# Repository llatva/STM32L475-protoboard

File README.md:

## STM32L475 protoboard

Development board for STM32L475 (4-layer board). Includes header for W5500 Ethernet module (SPI bus).

JP2 solder jumper needs to be short-circuited to enable USB VBUS detection (not needed if powered only from microUSB connector). Solder jumper needs to be short-circuited to enable USR1 LED. R8 is NOT to be mounted (USB data line pull-up is not used for this MCU type). Fuse pads are for polyswitch fuses. SMD capacitor pads are for A/D LPF (MCU pins have multiple functions).

Boot selection pin (BOOT0) next to the programming connector should be in normal operation shorted to GND (jumper). This means booting from FLASH.

Connector pinouts are documented on the bottom side of the board (programming interface, SPI interface).

See also the daughterboard, in the subdirectory "STM32daughter".

Designed by Lasse OH3HZB 2023

This work is licensed under a [Creative Commons Attribution-NonCommercial 4.0 International License (CC BY-NC 4.0)](https://creativecommons.org/licenses/by-nc/4.0/).

### RevA ERRATA

* Silkscreen: BOTTOM silkscreen, Ethernet connector's pin next to 3V3 is VDC, not "NC". Actual wiring is correct.

### 3D

### Photo

### Schematic

Open with KiCAD (v.7+) or use [this PDF](STM32L475-protoboard.pdf).

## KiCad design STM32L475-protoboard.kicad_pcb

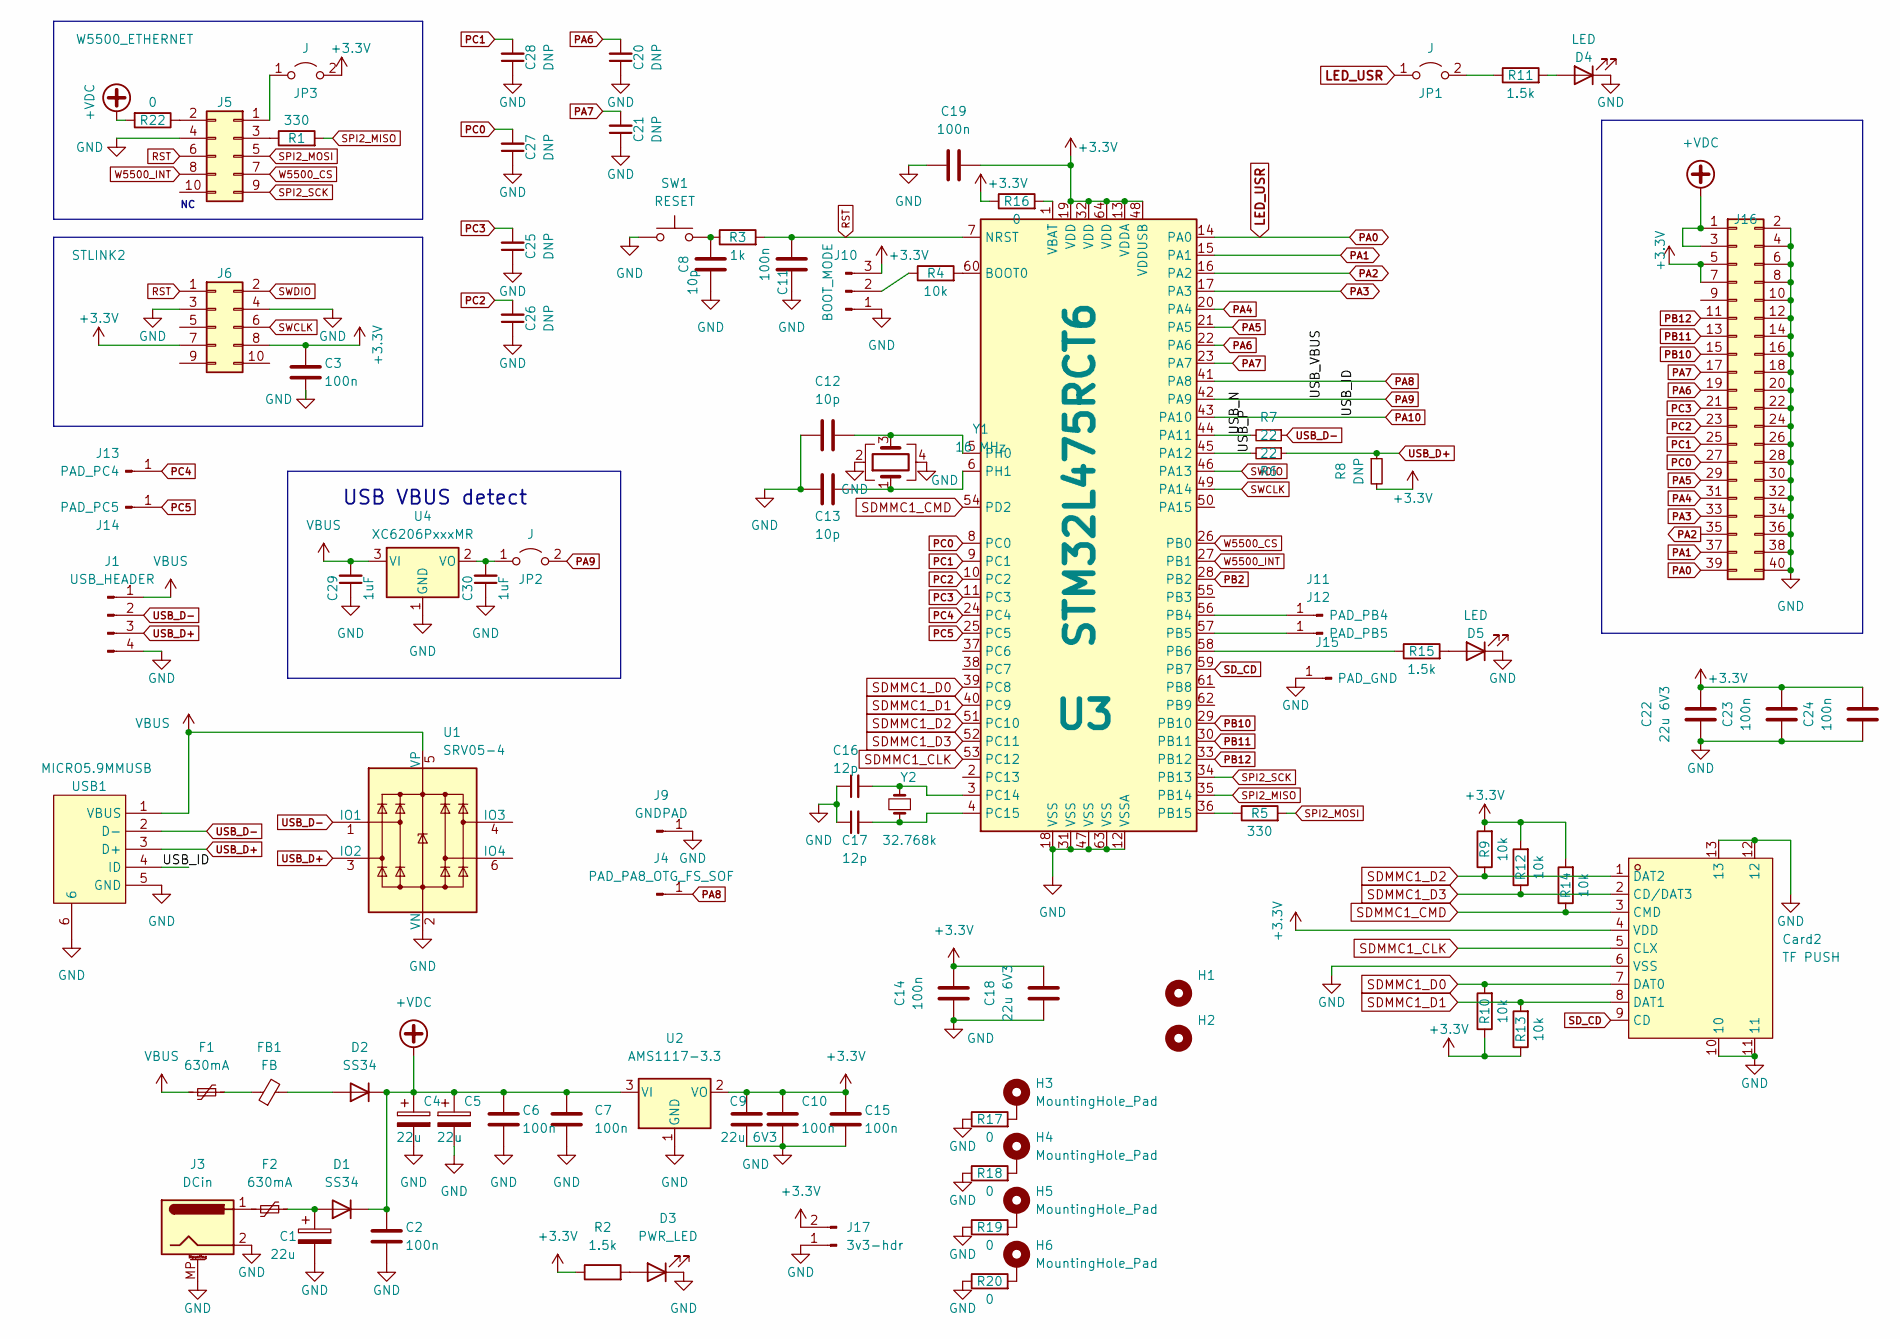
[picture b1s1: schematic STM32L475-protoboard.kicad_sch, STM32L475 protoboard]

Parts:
C1, C4, C5: 22u; C_0805_2012Metric; LCSC C45783
C2, C3, C6, C7, C10, C11, C14, C15, C19, C23, C24: 100n; C_0603_1608Metric; LCSC C14663
C8, C12, C13: 10p; C_0603_1608Metric; LCSC C1634
C9, C18, C22: 22u 6V3; C_0603_1608Metric; LCSC C59461
C16, C17: 12p; C_0603_1608Metric; LCSC C38523
C20, C21, C25, C26, C27, C28: DNP; C_1206_3216Metric_Pad1.33x1.80mm_HandSolder
C29, C30: 1uF; C_0603_1608Metric; LCSC C15849
Card2: TF PUSH; TF-SMD_TF-PUSH; LCSC Part C393941
D1, D2: SS34; D_SMA; LCSC C8678
D3: PWR_LED; LED_0805_2012Metric; LCSC C2297
D4, D5: LED; LED_0603_1608Metric; LCSC C2286
F1, F2: 630mA; R_Axial_DIN0207_L6.3mm_D2.5mm_P7.62mm_Horizontal
FB1: FB; L_0805_2012Metric; LCSC C1015
H1, H2: MountingHole_Pad; MountingHole_2.2mm_M2_DIN965_Pad_TopBottom
H3, H4, H5, H6: MountingHole_Pad; MountingHole_3.2mm_M3_DIN965_Pad_TopBottom
J1: USB_HEADER; PinHeader_1x04_P2.54mm_Vertical
J3: DCin; BarrelJack_Horizontal
J4: PAD_PA8_OTG_FS_SOF; SolderWirePad_1x01_SMD_1x2mm
J5: W5500_ETHERNET; PinSocket_2x05_P2.54mm_Vertical
J6: STLINK2; IDC-Header_2x05_P2.54mm_Vertical
J9: GNDPAD; SolderWirePad_1x01_SMD_1x2mm
J10: BOOT_MODE; PinHeader_1x03_P2.54mm_Vertical
J11: PAD_PB4; SolderWirePad_1x01_SMD_1x2mm
J12: PAD_PB5; SolderWirePad_1x01_SMD_1x2mm
J13: PAD_PC4; SolderWirePad_1x01_SMD_1x2mm
J14: PAD_PC5; SolderWirePad_1x01_SMD_1x2mm
J15: PAD_GND; SolderWirePad_1x01_SMD_1x2mm
J16: Conn_02x20_Odd_Even; PinHeader_2x20_P2.54mm_Vertical
J17: 3v3-hdr; PinHeader_1x02_P2.54mm_Vertical
JP1, JP2, JP3: J; SolderJumper-2_P1.3mm_Open_RoundedPad1.0x1.5mm
R1, R5: 330; R_0603_1608Metric; LCSC C23138
R2, R11, R15: 1.5k; R_0603_1608Metric; LCSC C22843
R3: 1k; R_0603_1608Metric_Pad0.98x0.95mm_HandSolder; LCSC C21190
R4, R9, R10, R12, R13, R14: 10k; R_0603_1608Metric; LCSC C25804
R6, R7: 22; R_0603_1608Metric; LCSC C23345
R8: DNP; R_0603_1608Metric_Pad0.98x0.95mm_HandSolder
R16, R17, R18, R19, R20, R22: 0; R_0603_1608Metric_Pad0.98x0.95mm_HandSolder; LCSC C21189
SW1: RESET; SW_PUSH_6mm_H4.3mm
U1: SRV05-4; SOT-23-6; LCSC C85364
U2: AMS1117-3.3; SOT-223-3_TabPin2; LCSC C6186
U3: STM32L475RCT6; LQFP-64_10x10mm_P0.5mm
U4: XC6206PxxxMR; SOT-23-3; LCSC C5446
USB1: MICRO5.9MMUSB; MICRO-USB-SMD_5P-P0.65-H-F_MICRO5.9MMUSB; LCSC C393940
Y1: 16 MHz; Crystal_SMD_3225-4Pin_3.2x2.5mm; LCSC C13738
Y2: 32.768k; Crystal_SMD_3215-2Pin_3.2x1.5mm; LCSC C32346

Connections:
+3V3: C3.1, C9.1, C10.1, C14.2, C15.1, C18.2, C19.2, C22.2, C23.2, C24.2, Card2.4 (VDD), J6.7, J6.8, J10.3, J16.5, J16.7, J17.2, JP3.2 (B), R2.1, R8.2, R9.2, R10.1, R12.2, R13.1, R14.2, R16.1, U2.2 (VO), U3.13 (VDDA), U3.19 (VDD), U3.32 (VDD), U3.48 (VDDUSB), U3.64 (VDD)
+VDC: C2.1, C4.1, C5.1, C6.1, C7.1, D1.1 (K), D2.1 (K), J16.1, J16.3, R22.2, U2.3 (VI)
/USB_N: R6.2, U3.44 (PA11)
/USB_P: R7.2, U3.45 (PA12)
GND: C1.2, C2.2, C3.2, C4.2, C5.2, C6.2, C7.2, C8.2, C9.2, C10.2, C11.1, C12.1, C13.2, C14.1, C15.2, C16.1, C17.1, C18.1, C19.1, C20.1, C21.1, C22.1, C23.1, C24.1, C25.1, C26.1, C27.1, C28.1, C29.1, C30.1, Card2.6 (VSS), Card2.10, Card2.11, Card2.12, Card2.13, D3.1 (K), D4.1 (K), D5.1 (K), J1.4, J3.2, J3.MP (MountPin), J5.4, J6.3, J6.4, J9.1, J10.1, J15.1, J16.2, J16.4, J16.6, J16.8, J16.10, J16.12, J16.14, J16.16, J16.18, J16.20, J16.22, J16.24, J16.26, J16.28, J16.30, J16.32, J16.34, J16.36, J16.38, J16.40, J17.1, R17.1, R18.1, R19.1, R20.1, SW1.1, U1.2 (VN), U2.1 (GND), U3.12 (VSSA), U3.18 (VSS), U3.31 (VSS), U3.47 (VSS), U3.63 (VSS), U4.1 (GND), USB1.5 (GND), USB1.6, Y1.2, Y1.4
LED_USR: J16.39, JP1.1 (A), U3.14 (PA0)
unnamed: C8.1, R3.1, SW1.2
unnamed: C1.1, D1.2 (A), F2.1
unnamed: D2.2 (A), FB1.2
unnamed: D3.2 (A), R2.2
unnamed: D4.2 (A), R11.2
unnamed: D5.2 (A), R15.2
unnamed: F1.1, FB1.1
unnamed: F2.2, J3.1
unnamed: H3.1, R17.2
unnamed: H4.1, R18.2
unnamed: H5.1, R19.2
unnamed: H6.1, R20.2
unnamed: J5.1, JP3.1 (A)
unnamed: J5.2, R22.1
unnamed: J5.3, R1.1
unnamed: J10.2, R4.1
unnamed: J11.1, U3.56 (PB4)
unnamed: J12.1, U3.57 (PB5)
unnamed: JP1.2 (B), R11.1
unnamed: C30.2, JP2.1 (A), U4.2 (VO)
unnamed: R4.2, U3.60 (BOOT0)
unnamed: R15.1, U3.58 (PB6)
unnamed: R5.1, U3.36 (PB15)
unnamed: C16.2, U3.3 (PC14), Y2.2
unnamed: C17.2, U3.4 (PC15), Y2.1
unnamed: C12.2, U3.5 (PH0), Y1.3
unnamed: C13.1, U3.6 (PH1), Y1.1
unnamed: R16.2, U3.1 (VBAT)
PA1: J16.37, U3.15 (PA1)
PA2: J16.35, U3.16 (PA2)
PA3: J16.33, U3.17 (PA3)
PA4: J16.31, U3.20 (PA4)
PA5: J16.29, U3.21 (PA5)
PA6: C20.2, J16.19, U3.22 (PA6)
PA7: C21.2, J16.17, U3.23 (PA7)
PA8: J4.1, U3.41 (PA8)
PA9: JP2.2 (B), U3.42 (PA9)
PA10: U3.43 (PA10), USB1.4 (ID)
PB2: U3.28 (PB2)
PB10: J16.15, U3.29 (PB10)
PB11: J16.13, U3.30 (PB11)
PB12: J16.11, U3.33 (PB12)
PC0: C27.2, J16.27, U3.8 (PC0)
PC1: C28.2, J16.25, U3.9 (PC1)
PC2: C26.2, J16.23, U3.10 (PC2)
PC3: C25.2, J16.21, U3.11 (PC3)
PC4: J13.1, U3.24 (PC4)
PC5: J14.1, U3.25 (PC5)
RST: C11.2, J5.6, J6.1, R3.2, U3.7 (NRST)
SDMMC1_CLK: Card2.5 (CLX), U3.53 (PC12)
SDMMC1_CMD: Card2.3 (CMD), R14.1, U3.54 (PD2)
SDMMC1_D0: Card2.7 (DAT0), R10.2, U3.39 (PC8)
SDMMC1_D1: Card2.8 (DAT1), R13.2, U3.40 (PC9)
SDMMC1_D2: Card2.1 (DAT2), R9.1, U3.51 (PC10)
SDMMC1_D3: Card2.2 (CD/DAT3), R12.1, U3.52 (PC11)
SD_CD: Card2.9 (CD), U3.59 (PB7)
SPI2_MISO: R1.2, U3.35 (PB14)
SPI2_MOSI: J5.5, R5.2
SPI2_SCK: J5.9, U3.34 (PB13)
SWCLK: J6.6, U3.49 (PA14)
SWDIO: J6.2, U3.46 (PA13)
USB_D+: J1.3, R7.1, R8.1, U1.3 (IO2), USB1.3 (D+)
USB_D-: J1.2, R6.1, U1.1 (IO1), USB1.2 (D-)
VBUS: C29.2, F1.2, J1.1, U1.5 (VP), U4.3 (VI), USB1.1 (VBUS)
W5500_CS: J5.7, U3.26 (PB0)
W5500_INT: J5.8, U3.27 (PB1)

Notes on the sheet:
USB VBUS detect

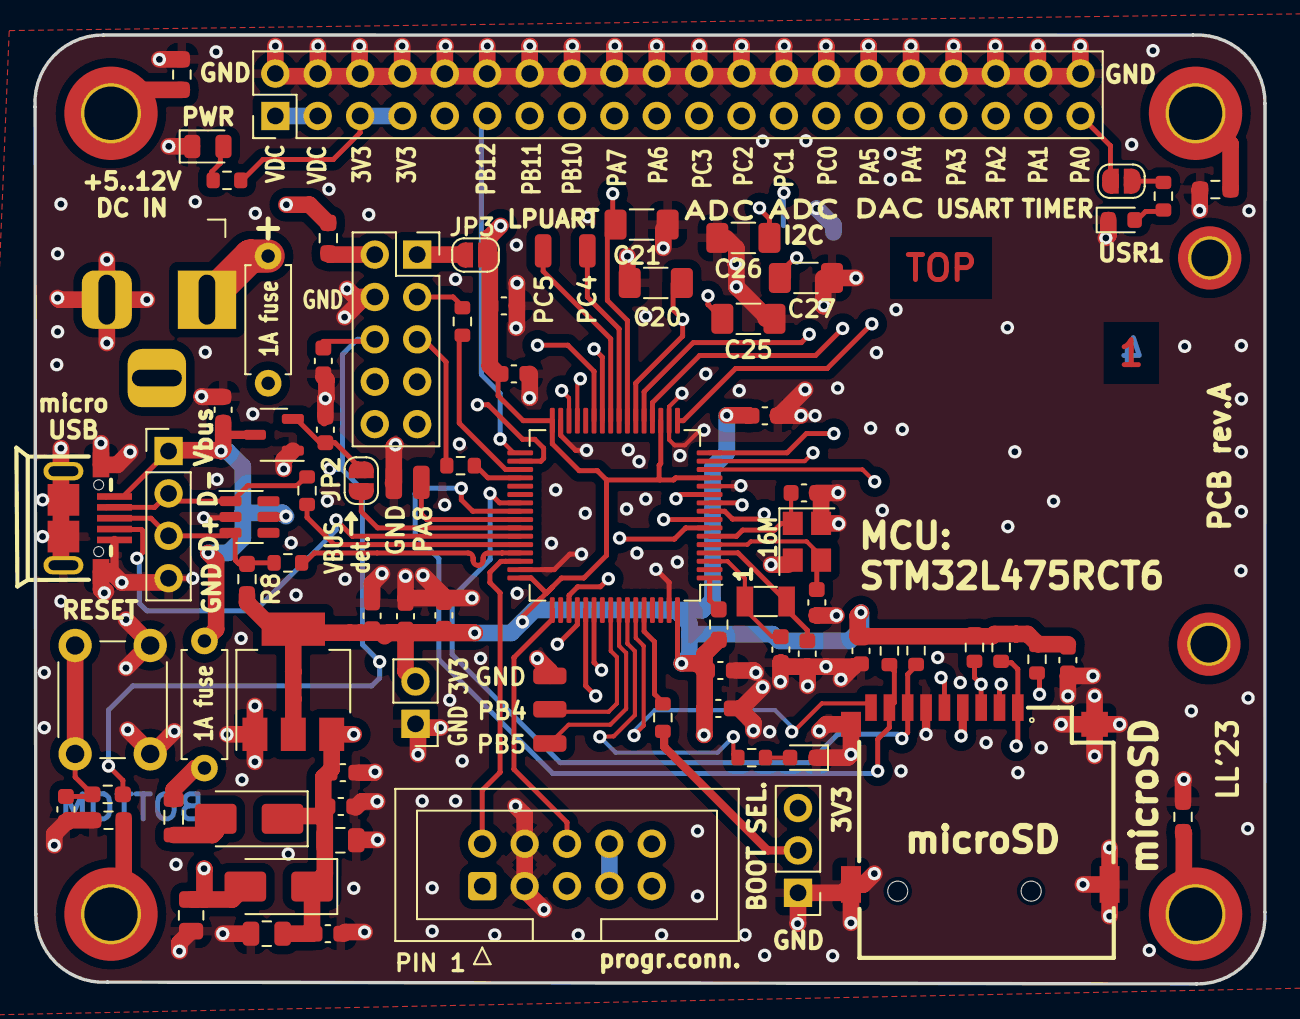
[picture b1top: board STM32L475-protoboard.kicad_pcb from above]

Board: 4 copper layers, 73.7 x 56.9 mm, 91 parts (1 on the bottom side), 71 nets.

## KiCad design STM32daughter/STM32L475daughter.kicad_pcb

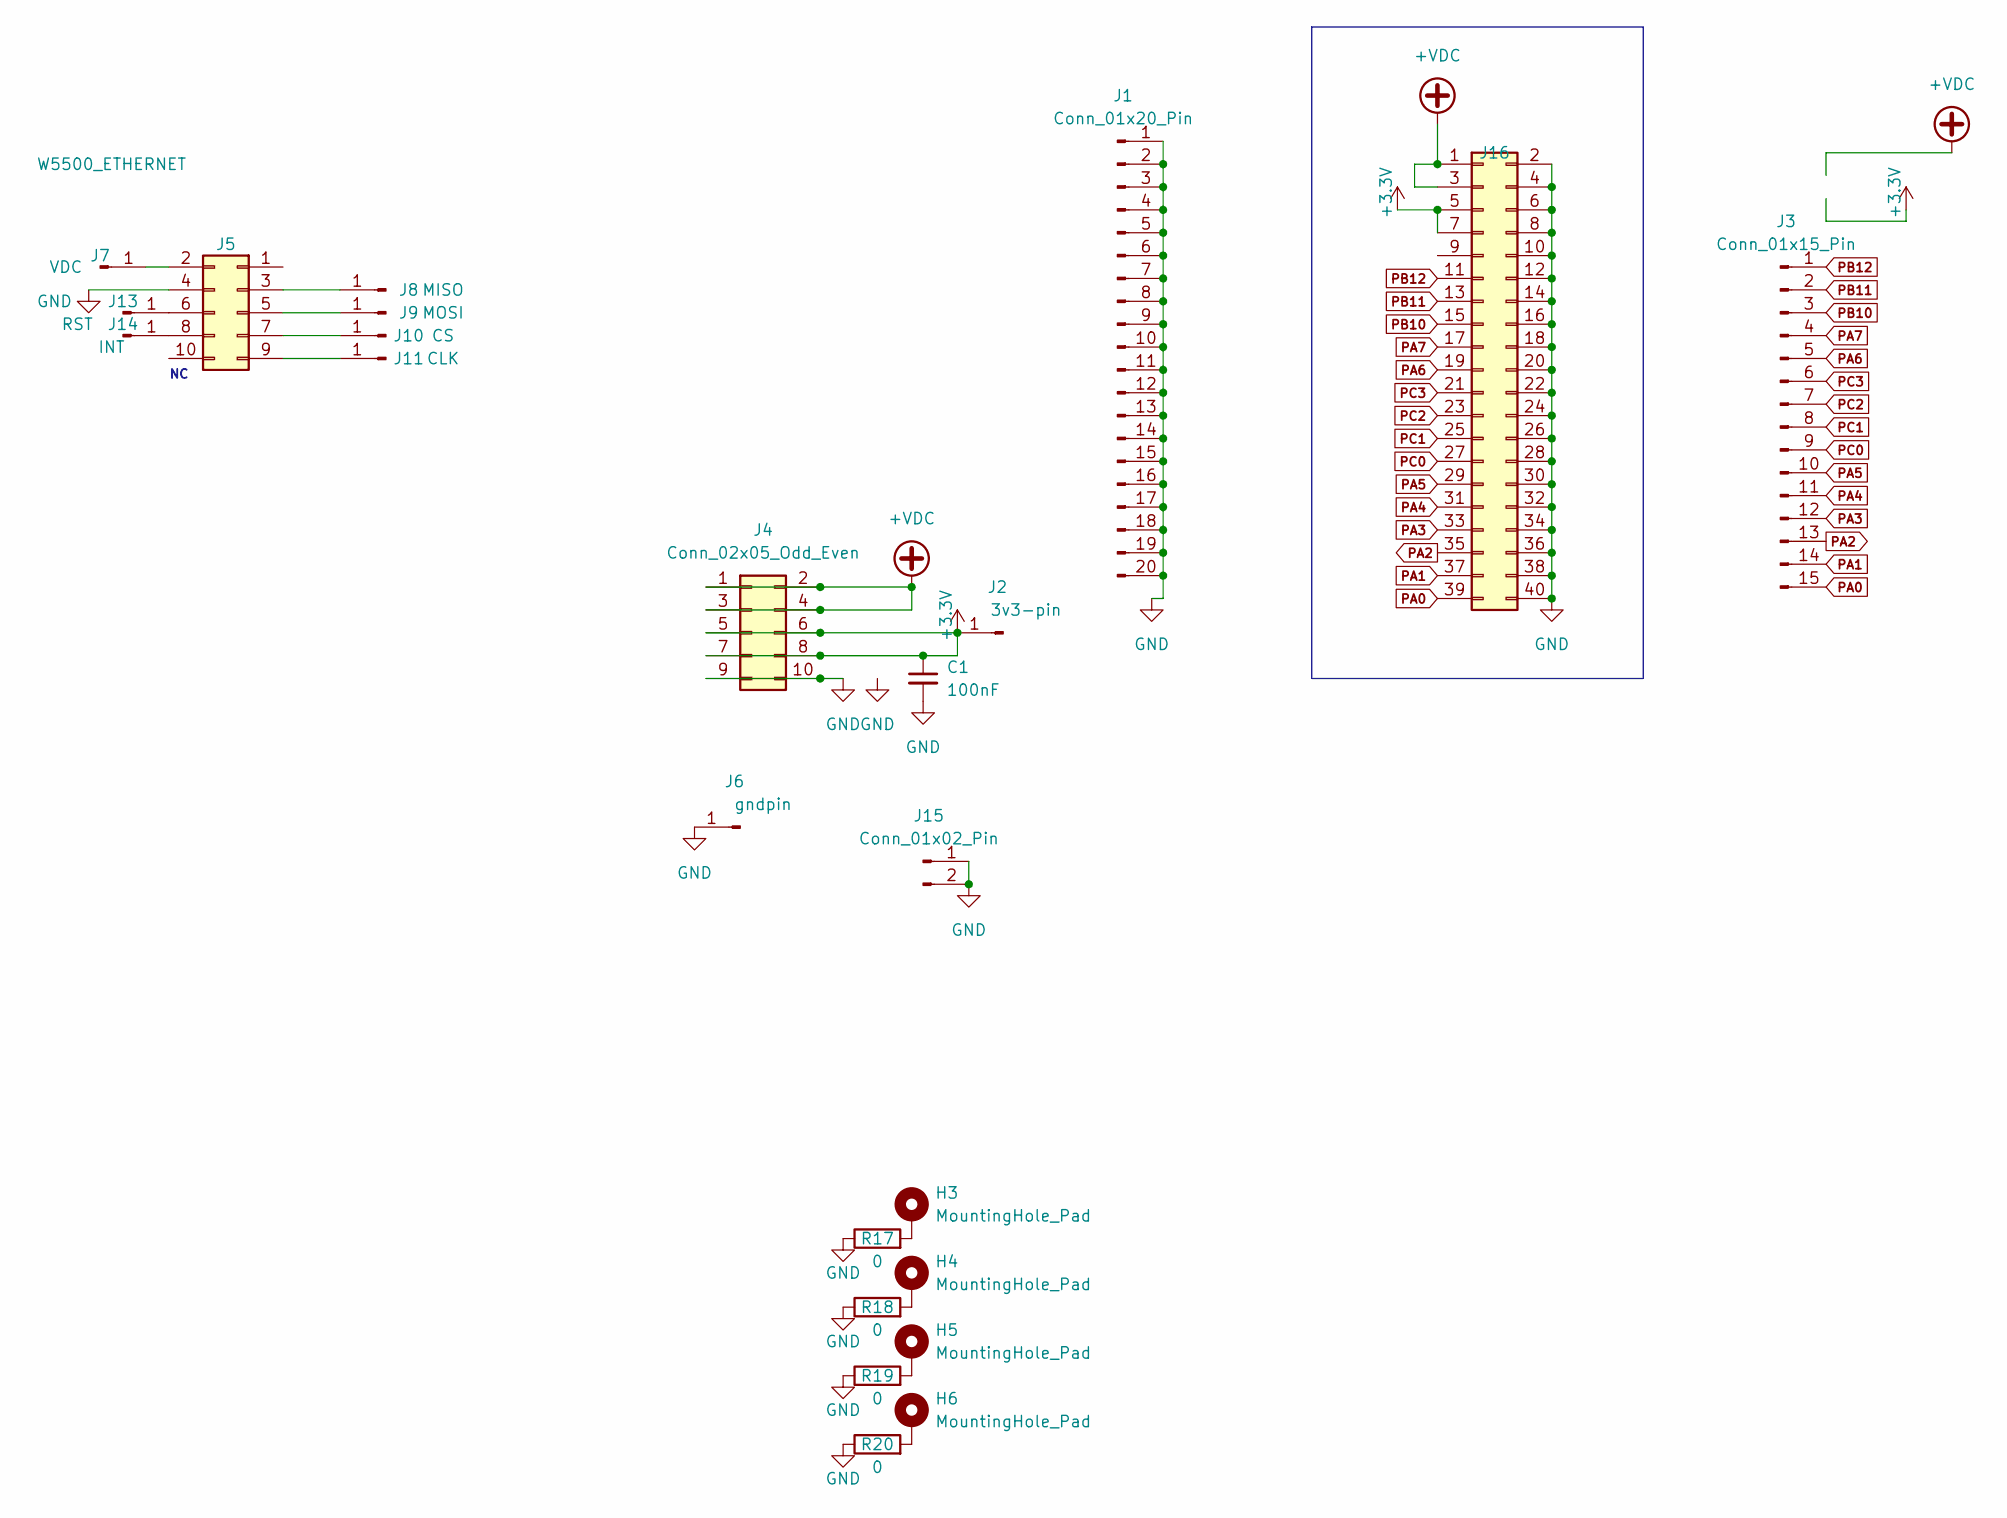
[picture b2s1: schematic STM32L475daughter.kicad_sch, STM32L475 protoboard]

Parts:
C1: 100nF; C_1206_3216Metric_Pad1.33x1.80mm_HandSolder
H3, H4, H5, H6: MountingHole_Pad; MountingHole_3.2mm_M3_DIN965_Pad_TopBottom
J1: Conn_01x20_Pin; PinHeader_1x20_P2.54mm_Vertical
J2: 3v3-pin; SolderWirePad_1x01_SMD_1x2mm
J3: Conn_01x15_Pin; PinHeader_1x15_P2.54mm_Vertical
J4: Conn_02x05_Odd_Even; PinHeader_2x05_P2.54mm_Vertical
J5: W5500_ETHERNET; PinSocket_2x05_P2.54mm_Vertical
J6: gndpin; SolderWirePad_1x01_SMD_1x2mm
J7: VDC; SolderWirePad_1x01_SMD_1x2mm
J8: MISO; SolderWirePad_1x01_SMD_1x2mm
J9: MOSI; SolderWirePad_1x01_SMD_1x2mm
J10: CS; SolderWirePad_1x01_SMD_1x2mm
J11: CLK; SolderWirePad_1x01_SMD_1x2mm
J13: RST; SolderWirePad_1x01_SMD_1x2mm
J14: INT; SolderWirePad_1x01_SMD_1x2mm
J15: Conn_01x02_Pin; PinHeader_1x02_P2.54mm_Vertical
J16: Conn_02x20_Odd_Even; PinHeader_2x20_P2.54mm_Vertical
R17, R18, R19, R20: 0; R_0603_1608Metric_Pad0.98x0.95mm_HandSolder; LCSC C21189

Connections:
+3V3: C1.1, J2.1, J4.5, J4.6, J4.7, J4.8, J16.5, J16.7
+VDC: J4.1, J4.2, J4.3, J4.4, J16.1, J16.3
GND: C1.2, J1.1, J1.2, J1.3, J1.4, J1.5, J1.6, J1.7, J1.8, J1.9, J1.10, J1.11, J1.12, J1.13, J1.14, J1.15, J1.16, J1.17, J1.18, J1.19, J1.20, J4.9, J4.10, J5.4, J6.1, J15.1, J15.2, J16.2, J16.4, J16.6, J16.8, J16.10, J16.12, J16.14, J16.16, J16.18, J16.20, J16.22, J16.24, J16.26, J16.28, J16.30, J16.32, J16.34, J16.36, J16.38, J16.40, R17.1, R18.1, R19.1, R20.1
unnamed: H3.1, R17.2
unnamed: H4.1, R18.2
unnamed: H5.1, R19.2
unnamed: H6.1, R20.2
unnamed: J5.2, J7.1
unnamed: J5.3, J8.1
unnamed: J5.5, J9.1
unnamed: J5.7, J10.1
unnamed: J5.9, J11.1
unnamed: J5.6, J13.1
unnamed: J5.8, J14.1
PA0: J3.15, J16.39
PA1: J3.14, J16.37
PA2: J3.13, J16.35
PA3: J3.12, J16.33
PA4: J3.11, J16.31
PA5: J3.10, J16.29
PA6: J3.5, J16.19
PA7: J3.4, J16.17
PB10: J3.3, J16.15
PB11: J3.2, J16.13
PB12: J3.1, J16.11
PC0: J3.9, J16.27
PC1: J3.8, J16.25
PC2: J3.7, J16.23
PC3: J3.6, J16.21

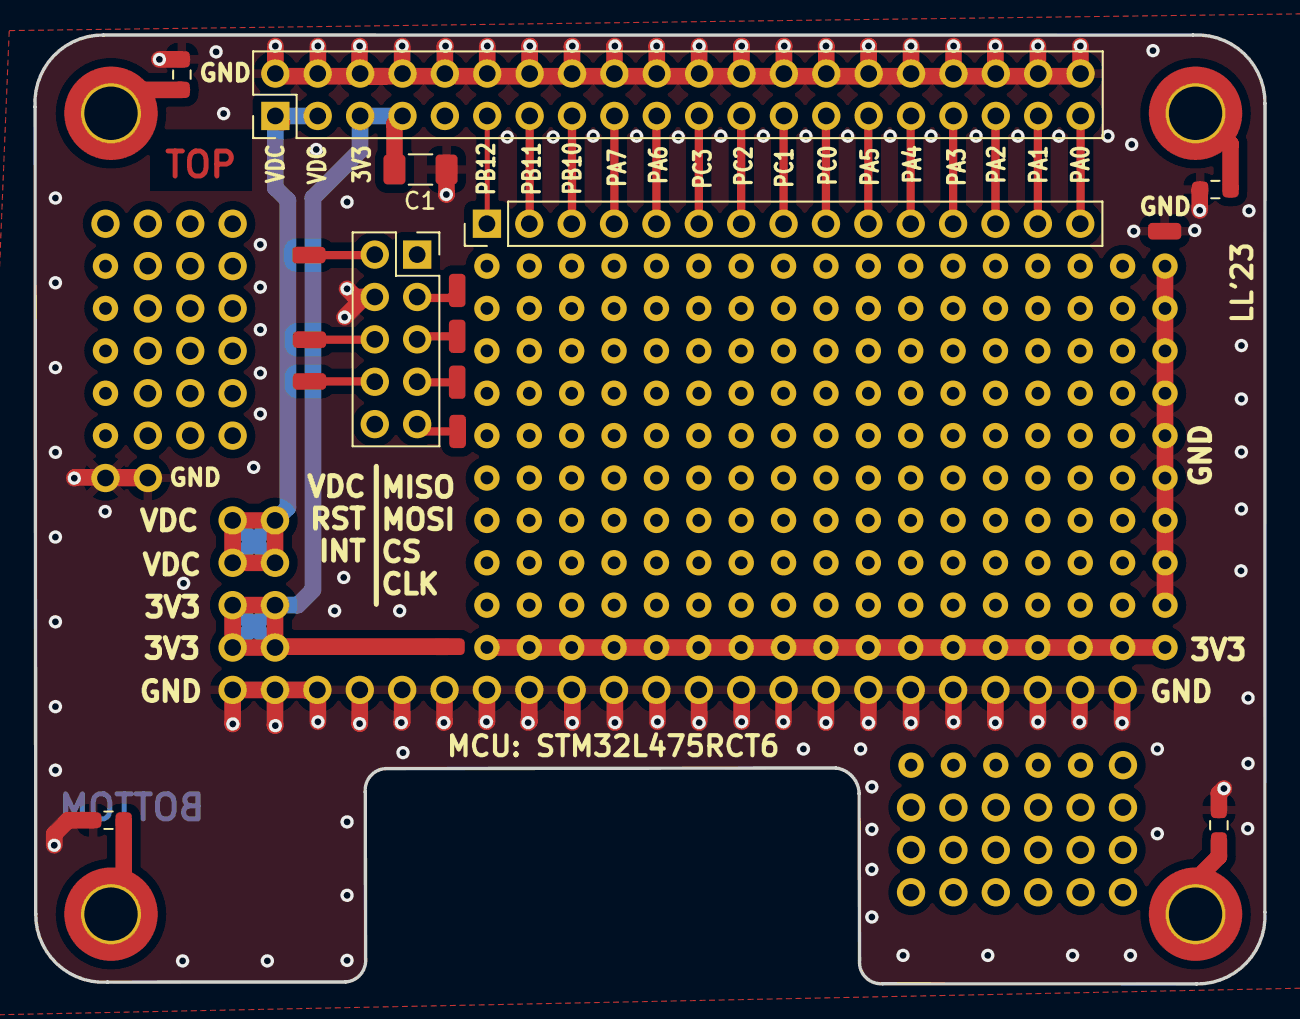
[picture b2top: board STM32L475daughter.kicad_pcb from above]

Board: 2 copper layers, 73.7 x 56.9 mm, 24 parts (0 on the bottom side), 29 nets.

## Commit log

2023-05-14 initial commit to github
2023-05-14 added .gitignore
2023-05-15 some progress
2023-05-19 littlebit further
2023-05-19 final commit for this session, to be continued
2023-05-20 save
2023-05-22 some notes to schema
2023-05-24 saveä
2023-05-24 STM32L475 should have internal pullup for USB line, but need to be checked (now DNP resistor)
2023-05-24 todo update
2023-05-24 layout
2023-05-24 note
2023-05-24 some fixes
2023-05-25 some routing
2023-05-25 some more pins
2023-05-25 texts
2023-05-25 SD -> microSD, w.i.p
2023-05-25 todo: find proper microSD connector from JLC
2023-05-29 moved mcu a littlebit left
2023-05-30 migration to KiCAD7
2023-05-30 microsd + misc
2023-05-30 to be continued next time
2023-06-01 misc routing
2023-06-01 to be continued
2023-06-02 almost there
2023-06-02 hole placement still to be fixed, leaving measurements visible
2023-06-02 fixed silk placement on bottom, long header
2023-06-03 mounting holes
2023-06-03 drc trace separtion checking
2023-06-03 micro usb connector change
2023-06-03 forgotted microUSB files + silk modifications to pcb
2023-06-03 schema pdf
2023-06-03 plot directory, schema printout
2023-06-03 minor fixes
2023-06-03 gerbers
2023-06-03 adjusted corners a littlebit
2023-06-03 fixed a couple of DRC errors
2023-06-03 lcsc code fixes
2023-06-04 daughterboard
2023-06-26 added 3D picture
2023-06-26 added license
2023-07-07 added photo
2023-07-07 Update README.md (added photo)
